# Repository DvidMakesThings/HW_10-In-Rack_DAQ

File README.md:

# DataForge-Pi - The Raspberry integrated DAQ Project

## Introduction

In the current market, finding a DAQ specifically designed for 10-inch racks is quite challenging. Most available options are tailored for 19-inch racks, which are significantly larger and not suitable for more compact setups. Recognizing this gap, I embarked on a project to create a DAQ solution that fits perfectly in a 10-inch rack while still providing all the necessary features and functionalities. The goal of this project is not only to address the size constraints but also to keep the costs low and make the design accessible to everyone. 

## Development Phases

| Phase                                | Status   |
| ------------------------------------ | -------- |
| **PCB Design & Prototyping**         |  |
| **Design Review**                    |  |
| **Enclosure Design**                 |  |
| **Order PCB**                        |  |
| **Prototyping and Hardware Testing** |  |
| **Initial Firmware Development**     |  |
| **Enclosure Testing & Ventilation**  |  |
| **Web-Based UI for Control**         |  |
| **Power Logging & Alerts**           |  |
| **Production Optimization**          |  |

## Features

Key features of the CM5 are as follows (for more details, refer to the [CM5 datasheet](docs/Datasheets/Raspberry-CM5_Datasheet.pdf)):

- Broadcom BCM2712, quad core Cortex-A76 (ARMv8) 64-bit SoC @ 2.4GHz
- Small Footprint 55mm × 40mm × 4.7mm module
  - 4 × M2.5 mounting holes
- 4kp60 HEVC decoder
- OpenGL ES 3.1 graphics, Vulkan 1.2
- Options for 2GB, 4GB, or 8GB LPDDR4-4267 SDRAM with ECC (see Appendix D)
- Options for 0GB (CM5Lite), 16GB, or 32GB eMMC flash memory (see Appendix D)
  - Peak eMMC bandwidth 400MBps (four times faster than previous Compute Modules)
- Option (see Appendix D) for certified radio module with:
  - 2.4 GHz, 5.0 GHz IEEE 802.11 b/g/n/ac wireless
  - Bluetooth 5.0, BLE
  - On board electronic switch to select between PCB trace or external antenna
- Gigabit Ethernet PHY supporting IEEE 1588
- 1 × PCIe 1-lane Host, Gen 2 (5Gbps)
- 1 × USB 2.0 port (high speed)
- 2 × USB 3.0 ports, supporting simultaneous 5Gbps operation
- Up to 30 × GPIO supporting either 1.8V or 3.3V signalling and peripheral options:
  - Up to 5 × UART
  - Up to 5 × I2C
  - Up to 5 × SPI
  - 1 × SDIO interface
  - 1 × DPI (parallel RGB display)
  - 1 × I2S
  - Up to 4 × PWM channels
  - Up to 3 × GPCLK outputs
- 2 × HDMI 2.0 ports (supports up to 4Kp60 on each port simultaneously)
- 2 × 4-lane MIPI ports
  - Supporting both DSI (display port) and CSI-2 (camera port)
- 1 × SDIO 2.0 (CM5Lite)
- Single +5V PSU input supports USB PD for up to 5A @ 5V
- Real-time clock (RTC), powered from external battery

## DAQ Specifications

### Analog Input (16 Channels)

The analog input section of the DAQ system is designed to provide high precision and flexibility for various applications. It features 16 channels of analog input, each capable of high-resolution data acquisition.

**Key Components:**
- **External 14-bit ADC:** The ADS9234RIRHBR is a 14-bit, 3.5-MSPS dual SAR ADC with simultaneous sampling, internal reference, and enhanced SPI, ensuring accurate and reliable measurements.
- **Multiplexers:** 2 × DG409 are employed for flexible channel selection, allowing the system to switch between different input channels efficiently.
- **Programmable Gain Amplifiers (PGA):** ADA4254ACPZ are used to provide scalable input ranges, enabling the system to handle a wide variety of signal amplitudes.

### Analog Output (8 Channels)

The analog output section is designed to provide precise and stable output signals. It features 8 channels of analog output, each capable of high-resolution signal generation.

**Key Components:**
- **External 16-bit DAC:** The DAC8568 is used for precision outputs, ensuring accurate and stable signal generation.
- **Operational Amplifiers:** TLV2372 are used for buffering and output stability, providing reliable and consistent performance.

### Digital IO (32 Channels)

The digital IO section is designed to provide versatile and robust digital input and output capabilities. It features 32 channels of digital IO, each capable of handling various voltage levels and signal types.

**Key Components:**
- **Bidirectional Voltage-Level Translators:** LSF0108-Q1 are used for multi-voltage compatibility, allowing the system to interface with different voltage levels.
- **Direct GPIO Support:** The RP2040 provides simple and robust design for direct GPIO support, ensuring reliable digital IO performance.

### Constants

- **ADC Sampling Rate:** 3.5 MSPS (Maximum sampling rate of ADS9234R)
- **ADC Nyquist Limit:** 1.75 MHz (Nyquist bandwidth for ADC)
- **PGA Bandwidth:** 10 MHz (Maximum bandwidth of ADA4254 at Gain = 1)
- **DG409 Transition Time:** 160 ns (Transition time for DG409)
- **ADA4254 Transition Time:** 200 ns (Transition time for ADA4254)

### Bandwidth for Each Gain Setting

The bandwidth for each gain setting is determined by the combination of the ADC's Nyquist limit and the PGA's frequency response. For gains less than or equal to 1, the bandwidth is capped by the ADC's Nyquist limit. For gains greater than 1, the bandwidth is limited by the PGA's frequency response.

- **Gain = 1/16:** Bandwidth = 1.75 MHz (Capped by ADC)
- **Gain = 1/8:** Bandwidth = 1.75 MHz (Capped by ADC)
- **Gain = 1/4:** Bandwidth = 1.75 MHz (Capped by ADC)
- **Gain = 1/2:** Bandwidth = 1.75 MHz (Capped by ADC)
- **Gain = 1:** Bandwidth = 1.75 MHz (Capped by ADC)
- **Gain = 2:** Bandwidth = 1.75 MHz (Capped by ADC)
- **Gain = 4:** Bandwidth = 1.75 MHz (Capped by ADC)
- **Gain = 8:** Bandwidth = 1.25 MHz (PGA Limited)
- **Gain = 16:** Bandwidth = 625 kHz (PGA Limited)
- **Gain = 32:** Bandwidth = 312.5 kHz (PGA Limited)
- **Gain = 64:** Bandwidth = 156.25 kHz (PGA Limited)
- **Gain = 128:** Bandwidth = 78.125 kHz (PGA Limited)

### Notes

- For Gains ≤ 1, bandwidth is capped by ADC's Nyquist limit (1.75 MHz).
- For Gains > 1, bandwidth is limited by the PGA's frequency response.
- Transition delays (DG409 + ADA4254) are factored into the calculation.

### Input Ranges for Different Gains

The input ranges for different gain settings are determined by the reference voltage (VREF), positive supply voltage (V+), and negative supply voltage (V-). For this system, VREF is set to 2.5V, V+ is set to +12V, and V- is set to -12V.

| Gain | Differential Input Range (±V) | Positive Input Range (0 to V) | Negative Input Range (0 to -V) | Max Bandwidth (Hz) |
|------|-------------------------------|-------------------------------|-------------------------------|--------------------|
| 1/16 | ±80.0                         | 0 to 40.0                     | 0 to -40.0                    | 1,750,000          |
| 1/8  | ±40.0                         | 0 to 20.0                     | 0 to -20.0                    | 1,750,000          |
| 1/4  | ±20.0                         | 0 to 10.0                     | 0 to -10.0                    | 1,750,000          |
| 1/2  | ±10.0                         | 0 to 5.0                      | 0 to -5.0                     | 1,750,000          |
| 1    | ±5.0                          | 0 to 2.5                      | 0 to -2.5                     | 1,750,000          |
| 2    | ±2.5                          | 0 to 1.25                     | 0 to -1.25                    | 1,750,000          |
| 4    | ±1.25                         | 0 to 0.625                    | 0 to -0.625                   | 1,750,000          |
| 8    | ±0.625                        | 0 to 0.3125                   | 0 to -0.3125                  | 1,250,000          |
| 16   | ±0.3125                       | 0 to 0.15625                  | 0 to -0.15625                 | 625,000            |
| 32   | ±0.15625                      | 0 to 0.078125                 | 0 to -0.078125                | 312,500            |
| 64   | ±0.078125                     | 0 to 0.0390625                | 0 to -0.0390625               | 156,250            |
| 128  | ±0.0390625                    | 0 to 0.01953125               | 0 to -0.01953125              | 78,125             |

## Getting Started

Refer to the datasheets and manuals in the `docs` folder for detailed information on the components and usage instructions.

## License

This project is licensed under the GPL3 License. See the LICENSE file for details.

## Contact

For questions or feedback:

- Email: s.dvid@hotmail.com
- GitHub: [DvidMakesThings](https://github.com/DvidMakesThings)

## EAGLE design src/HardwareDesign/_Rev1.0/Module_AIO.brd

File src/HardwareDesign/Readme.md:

# # %PROJECT_NAME% Project Hardware Design Files
## Contents
This folder contains the hardware design files for the %PROJECT_NAME% project. The main components include:
- Schematic diagrams
- PCB layouts
- Bill of Materials (BOM)
- Gerber files
## Usage
To use these hardware design files:
1. Open the schematic diagrams and PCB layouts using EAGLE software.
2. Review the Bill of Materials for required components.
3. Follow the design files to assemble and test the hardware.
4. Use the Gerber files for PCB manufacturing.
## License
This project is licensed under the MIT License.
## Contact
For any questions or feedback, please contact:
- Email: [s.dvid@hotmail.com](mailto:s.dvid@hotmail.com)
- GitHub: [DvidMakesThings](https://github.com/DvidMakesThings)

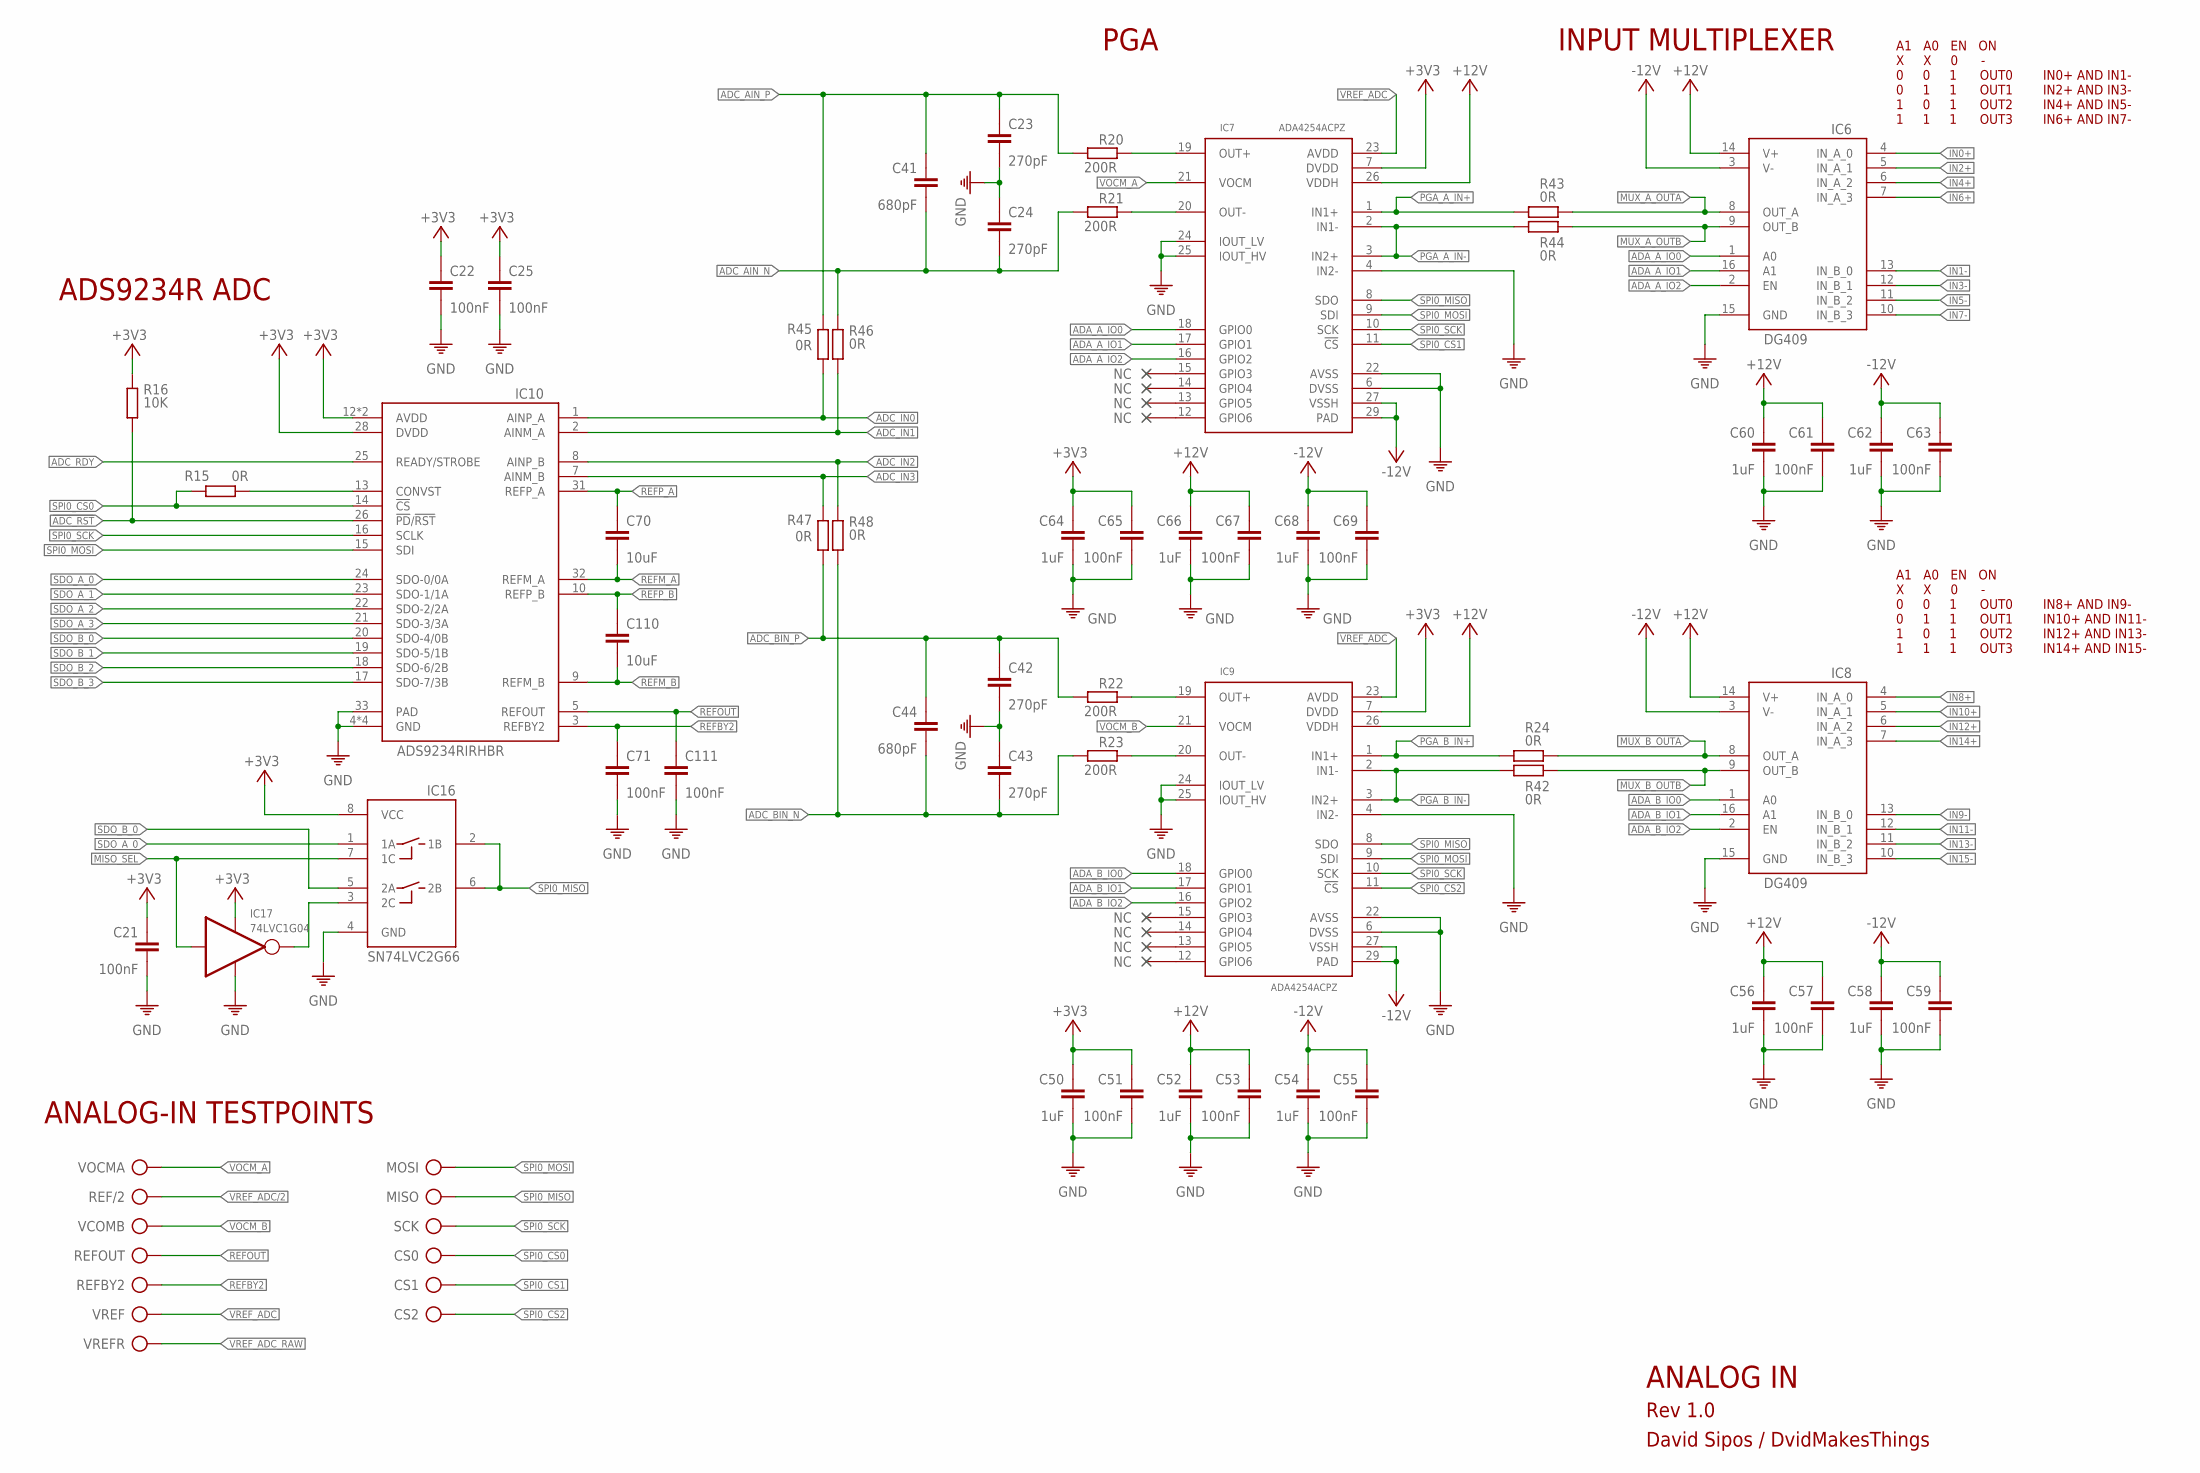
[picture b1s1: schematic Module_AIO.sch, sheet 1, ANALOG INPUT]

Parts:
C21, C22, C25, C51, C53, C55, C57, C59, C61, C63, C65, C67, C69, C71, C111: 100nF; C0402
C23, C24, C42, C43: 270pF; C0402
C41, C44: 680pF; C0402
C50, C52, C54, C56, C58, C60, C62, C64, C66, C68: 1uF; C0402
C70, C110: 10uF; C0402
CS0, CS1, CS2: TP
IC6, IC8: DG409; TSSOP2
IC7, IC9: ADA4254ACPZ; QFN50P500X500X75-29T314N
IC10: ADS9234RIRHBR; VQFN32-5X5
IC16: SN74LVC2G66; SOP50P310X90-8N
IC17: 74LVC1G04; SOT95P280X145-5N
MISO: TP
MOSI: TP
R15, R24, R42, R43, R44, R45, R46, R47, R48: 0R; 0402
R16: 10K; 0402
R20, R21, R22, R23: 200R; 0402
REF/2: TP
REFBY2: TP
REFOUT: TP
SCK: TP
VCOMB: TP
VOCMA: TP
VREF: TP
VREFR: TP

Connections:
!ADC_RST: IC10.26 (!PD!/!RST), R16.2; also elsewhere on the board
!MISO_SEL: IC16.3 (2C), IC17.4 (OUT)
+3V3: C21.1, C22.1, C25.1, C50.1, C51.1, C64.1, C65.1, IC7.7 (DVDD), IC9.7 (DVDD), IC10.12 (AVDD), IC10.28 (DVDD), IC10.29 (AVDD), IC16.8 (VCC), IC17.5 (V+), R16.1; also elsewhere on the board
+12V: C52.1, C53.1, C56.1, C57.1, C60.1, C61.1, C66.1, C67.1, IC6.14 (V+), IC7.26 (VDDH), IC8.14 (V+), IC9.26 (VDDH); also elsewhere on the board
-12V: C54.1, C55.1, C58.1, C59.1, C62.1, C63.1, C68.1, C69.1, IC6.3 (V-), IC7.27 (VSSH), IC7.29 (PAD), IC8.3 (V-), IC9.27 (VSSH), IC9.29 (PAD); also elsewhere on the board
ADA_A_IO0: IC6.1 (A0), IC7.18 (GPIO0)
ADA_A_IO1: IC6.16 (A1), IC7.17 (GPIO1)
ADA_A_IO2: IC6.2 (EN), IC7.16 (GPIO2)
ADA_B_IO0: IC8.1 (A0), IC9.18 (GPIO0)
ADA_B_IO1: IC8.16 (A1), IC9.17 (GPIO1)
ADA_B_IO2: IC8.2 (EN), IC9.16 (GPIO2)
ADC_AIN_N: C24.2, C41.2, R21.1, R46.1
ADC_AIN_P: C23.1, C41.1, R20.1, R45.2
ADC_BIN_N: C43.2, C44.2, R23.1, R48.2
ADC_BIN_P: C42.1, C44.1, R22.1, R47.1
ADC_IN0: IC10.1 (AINP_A), R45.1
ADC_IN1: IC10.2 (AINM_A), R46.2
ADC_IN2: IC10.8 (AINP_B), R48.1
ADC_IN3: IC10.7 (AINM_B), R47.2
ADC_RDY: IC10.25 (READY/STROBE); also elsewhere on the board
GND: C21.2, C22.2, C23.2, C24.1, C25.2, C42.2, C43.1, C50.2, C51.2, C52.2, C53.2, C54.2, C55.2, C56.2, C57.2, C58.2, C59.2, C60.2, C61.2, C62.2, C63.2, C64.2, C65.2, C66.2, C67.2, C68.2, C69.2, C71.2, C111.2, IC6.15 (GND), IC7.4 (IN2-), IC7.6 (DVSS), IC7.22 (AVSS), IC7.24 (IOUT_LV), IC7.25 (IOUT_HV), IC8.15 (GND), IC9.4 (IN2-), IC9.6 (DVSS), IC9.22 (AVSS), IC9.24 (IOUT_LV), IC9.25 (IOUT_HV), IC10.4 (GND), IC10.11 (GND), IC10.27 (GND), IC10.30 (GND), IC10.33 (PAD), IC16.4 (GND), IC17.3 (V-); also elsewhere on the board
IN0+: IC6.4 (IN_A_0); also elsewhere on the board
IN1-: IC6.13 (IN_B_0); also elsewhere on the board
IN2+: IC6.5 (IN_A_1); also elsewhere on the board
IN3-: IC6.12 (IN_B_1); also elsewhere on the board
IN4+: IC6.6 (IN_A_2); also elsewhere on the board
IN5-: IC6.11 (IN_B_2); also elsewhere on the board
IN6+: IC6.7 (IN_A_3); also elsewhere on the board
IN7-: IC6.10 (IN_B_3); also elsewhere on the board
IN8+: IC8.4 (IN_A_0); also elsewhere on the board
IN9-: IC8.13 (IN_B_0); also elsewhere on the board
IN10+: IC8.5 (IN_A_1); also elsewhere on the board
IN11-: IC8.12 (IN_B_1); also elsewhere on the board
IN12+: IC8.6 (IN_A_2); also elsewhere on the board
IN13-: IC8.11 (IN_B_2); also elsewhere on the board
IN14+: IC8.7 (IN_A_3); also elsewhere on the board
IN15-: IC8.10 (IN_B_3); also elsewhere on the board
MISO_SEL: IC16.7 (1C), IC17.2 (IN); also elsewhere on the board
MUX_A_OUTA: IC6.8 (OUT_A), R43.2
MUX_A_OUTB: IC6.9 (OUT_B), R44.1
MUX_B_OUTA: IC8.8 (OUT_A), R24.2
MUX_B_OUTB: IC8.9 (OUT_B), R42.1
unnamed: IC7.19 (OUT+), R20.2
unnamed: IC7.20 (OUT-), R21.2
unnamed: IC9.19 (OUT+), R22.2
unnamed: IC9.20 (OUT-), R23.2
unnamed: IC10.13 (CONVST), R15.2
PGA_A_IN+: IC7.1 (IN1+), R43.1
PGA_A_IN-: IC7.2 (IN1-), IC7.3 (IN2+), R44.2
PGA_B_IN+: IC9.1 (IN1+), R24.1
PGA_B_IN-: IC9.2 (IN1-), IC9.3 (IN2+), R42.2
REFBY2: C71.1, IC10.3 (REFBY2), REFBY2.TP
REFM_A: C70.2, IC10.32 (REFM_A)
REFM_B: C110.2, IC10.9 (REFM_B)
REFOUT: C111.1, IC10.5 (REFOUT), REFOUT.TP
REFP_A: C70.1, IC10.31 (REFP_A)
REFP_B: C110.1, IC10.10 (REFP_B)
SDO_A_0: IC10.24 (SDO-0/0A), IC16.1 (1A); also elsewhere on the board
SDO_A_1: IC10.23 (SDO-1/1A); also elsewhere on the board
SDO_A_2: IC10.22 (SDO-2/2A); also elsewhere on the board
SDO_A_3: IC10.21 (SDO-3/3A); also elsewhere on the board
SDO_B_0: IC10.20 (SDO-4/0B), IC16.5 (2A); also elsewhere on the board
SDO_B_1: IC10.19 (SDO-5/1B); also elsewhere on the board
SDO_B_2: IC10.18 (SDO-6/2B); also elsewhere on the board
SDO_B_3: IC10.17 (SDO-7/3B); also elsewhere on the board
SPI0_CS0: CS0.TP, IC10.14 (!CS), R15.1; also elsewhere on the board
SPI0_CS1: CS1.TP, IC7.11 (!CS); also elsewhere on the board
SPI0_CS2: CS2.TP, IC9.11 (!CS); also elsewhere on the board
SPI0_MISO: IC7.8 (SDO), IC9.8 (SDO), IC16.2 (1B), IC16.6 (2B), MISO.TP; also elsewhere on the board
SPI0_MOSI: IC7.9 (SDI), IC9.9 (SDI), IC10.15 (SDI), MOSI.TP; also elsewhere on the board
SPI0_SCK: IC7.10 (SCK), IC9.10 (SCK), IC10.16 (SCLK), SCK.TP; also elsewhere on the board
VOCM_A: IC7.21 (VOCM), VOCMA.TP; also elsewhere on the board
VOCM_B: IC9.21 (VOCM), VCOMB.TP; also elsewhere on the board
VREF_ADC: IC7.23 (AVDD), IC9.23 (AVDD), VREF.TP; also elsewhere on the board
VREF_ADC/2: REF/2.TP; also elsewhere on the board
VREF_ADC_RAW: VREFR.TP; also elsewhere on the board

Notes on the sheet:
ADS9234R ADC
A1 A0 EN ON
X X 0 -
0 0 1 OUT0
0 1 1 OUT1
1 0 1 OUT2
1 1 1 OUT3
IN0+ AND IN1-
IN2+ AND IN3-
IN4+ AND IN5-
IN6+ AND IN7-
IN8+ AND IN9-
IN10+ AND IN11-
IN12+ AND IN13-
IN14+ AND IN15-
ANALOG-IN TESTPOINTS
PGA
INPUT MULTIPLEXER
ANALOG IN
Rev 1.0
David Sipos / DvidMakesThings

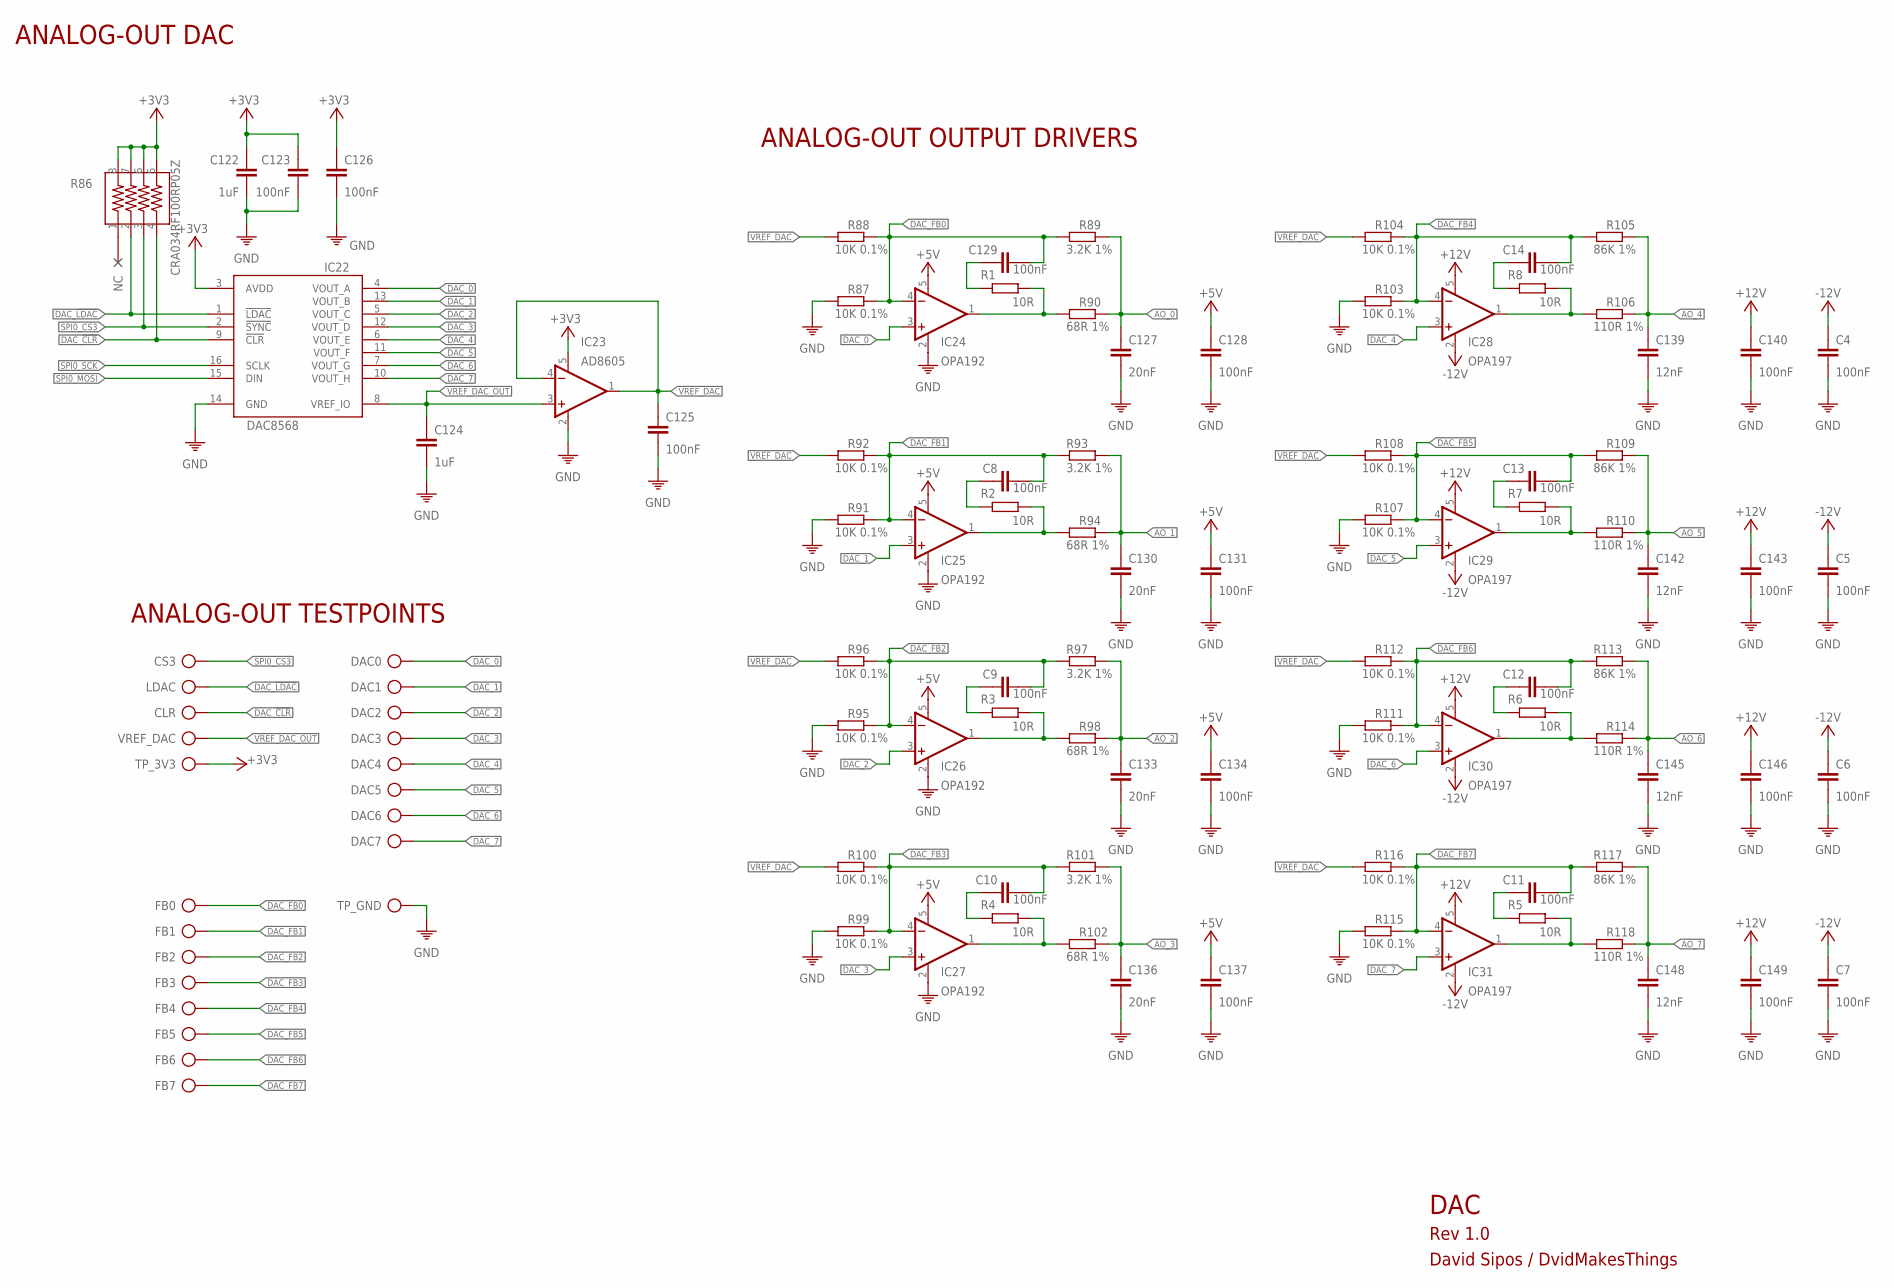
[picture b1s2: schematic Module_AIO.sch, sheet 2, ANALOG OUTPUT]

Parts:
C4, C5, C6, C7, C8, C9, C10, C11, C12, C13, C14, C123, C125, C126, C128, C129, C131, C134, C137, C140, C143, C146, C149: 100nF; C0402
C122, C124: 1uF; C0402
C127, C130, C133, C136: 20nF; C0402
C139, C142, C145, C148: 12nF; C0402
CLR: TP
CS3: TP
DAC0, DAC1, DAC2, DAC3, DAC4, DAC5, DAC6, DAC7: TP
FB0, FB1, FB2, FB3, FB4, FB5, FB6, FB7: TP
IC22: DAC8568; TSSOP16
IC23: AD8605; SOT23-5
IC24, IC25, IC26, IC27: OPA192; SOT23-5
IC28, IC29, IC30, IC31: OPA197; SOT23-5
LDAC: TP
R1, R2, R3, R4, R5, R6, R7, R8: 10R; 0402
R86: CRA034RF100RP05Z; YC164-JR-0733RL
R87, R88, R91, R92, R95, R96, R99, R100, R103, R104, R107, R108, R111, R112, R115, R116: 10K 0.1%; 0402
R89, R93, R97, R101: 3.2K 1%; 0402
R90, R94, R98, R102: 68R 1%; 0402
R105, R109, R113, R117: 86K 1%; 0402
R106, R110, R114, R118: 110R 1%; 0402
TP_3V3: TP
TP_GND: TP
VREF_DAC: TP

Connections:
+3V3: C122.1, C123.1, C126.1, IC22.3 (AVDD), IC23.5 (V+), R86.5, R86.6, R86.7, R86.8, TP_3V3.TP; also elsewhere on the board
+5V: C128.1, C131.1, C134.1, C137.1, IC24.5 (V+), IC25.5 (V+), IC26.5 (V+), IC27.5 (V+); also elsewhere on the board
+12V: C140.1, C143.1, C146.1, C149.1, IC28.5 (V+), IC29.5 (V+), IC30.5 (V+), IC31.5 (V+); also elsewhere on the board
-12V: C4.1, C5.1, C6.1, C7.1, IC28.2 (V-), IC29.2 (V-), IC30.2 (V-), IC31.2 (V-); also elsewhere on the board
AO_0: C127.1, R89.2, R90.2; also elsewhere on the board
AO_1: C130.1, R93.2, R94.2; also elsewhere on the board
AO_2: C133.1, R97.2, R98.2; also elsewhere on the board
AO_3: C136.1, R101.2, R102.2; also elsewhere on the board
AO_4: C139.1, R105.2, R106.2; also elsewhere on the board
AO_5: C142.1, R109.2, R110.2; also elsewhere on the board
AO_6: C145.1, R113.2, R114.2; also elsewhere on the board
AO_7: C148.1, R117.2, R118.2; also elsewhere on the board
DAC_0: DAC0.TP, IC22.4 (VOUT_A), IC24.3 (+IN)
DAC_1: DAC1.TP, IC22.13 (VOUT_B), IC25.3 (+IN)
DAC_2: DAC2.TP, IC22.5 (VOUT_C), IC26.3 (+IN)
DAC_3: DAC3.TP, IC22.12 (VOUT_D), IC27.3 (+IN)
DAC_4: DAC4.TP, IC22.6 (VOUT_E), IC28.3 (+IN)
DAC_5: DAC5.TP, IC22.11 (VOUT_F), IC29.3 (+IN)
DAC_6: DAC6.TP, IC22.7 (VOUT_G), IC30.3 (+IN)
DAC_7: DAC7.TP, IC22.10 (VOUT_H), IC31.3 (+IN)
DAC_!CLR: CLR.TP, IC22.9 (!CLR), R86.4; also elsewhere on the board
DAC_!LDAC: IC22.1 (!LDAC), LDAC.TP, R86.2; also elsewhere on the board
DAC_FB0: C129.2, FB0.TP, IC24.4 (-IN), R87.2, R88.2, R89.1
DAC_FB1: C8.2, FB1.TP, IC25.4 (-IN), R91.2, R92.2, R93.1
DAC_FB2: C9.2, FB2.TP, IC26.4 (-IN), R95.2, R96.2, R97.1
DAC_FB3: C10.2, FB3.TP, IC27.4 (-IN), R99.2, R100.2, R101.1
DAC_FB4: C14.2, FB4.TP, IC28.4 (-IN), R103.2, R104.2, R105.1
DAC_FB5: C13.2, FB5.TP, IC29.4 (-IN), R107.2, R108.2, R109.1
DAC_FB6: C12.2, FB6.TP, IC30.4 (-IN), R111.2, R112.2, R113.1
DAC_FB7: C11.2, FB7.TP, IC31.4 (-IN), R115.2, R116.2, R117.1
GND: C4.2, C5.2, C6.2, C7.2, C122.2, C123.2, C124.2, C125.2, C126.2, C127.2, C128.2, C130.2, C131.2, C133.2, C134.2, C136.2, C137.2, C139.2, C140.2, C142.2, C143.2, C145.2, C146.2, C148.2, C149.2, IC22.14 (GND), IC23.2 (V-), IC24.2 (V-), IC25.2 (V-), IC26.2 (V-), IC27.2 (V-), R87.1, R91.1, R95.1, R99.1, R103.1, R107.1, R111.1, R115.1, TP_GND.TP; also elsewhere on the board
unnamed: C129.1, R1.2
unnamed: C8.1, R2.2
unnamed: C9.1, R3.2
unnamed: C10.1, R4.2
unnamed: IC24.1 (OUT), R1.1, R90.1
unnamed: C11.1, R5.2
unnamed: IC25.1 (OUT), R2.1, R94.1
unnamed: C12.1, R6.2
unnamed: IC26.1 (OUT), R3.1, R98.1
unnamed: IC27.1 (OUT), R4.1, R102.1
unnamed: C13.1, R7.2
unnamed: IC28.1 (OUT), R8.1, R106.1
unnamed: IC29.1 (OUT), R7.1, R110.1
unnamed: C14.1, R8.2
unnamed: IC30.1 (OUT), R6.1, R114.1
unnamed: IC31.1 (OUT), R5.1, R118.1
SPI0_CS3: CS3.TP, IC22.2 (!SYNC), R86.3; also elsewhere on the board
SPI0_MOSI: IC22.15 (DIN); also elsewhere on the board
SPI0_SCK: IC22.16 (SCLK); also elsewhere on the board
VREF_DAC: C125.1, IC23.1 (OUT), IC23.4 (-IN), R88.1, R92.1, R96.1, R100.1, R104.1, R108.1, R112.1, R116.1
VREF_DAC_OUT: C124.1, IC22.8 (VREF_IO), IC23.3 (+IN), VREF_DAC.TP

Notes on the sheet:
ANALOG-OUT TESTPOINTS
ANALOG-OUT DAC
ANALOG-OUT OUTPUT DRIVERS
DAC
Rev 1.0
David Sipos / DvidMakesThings

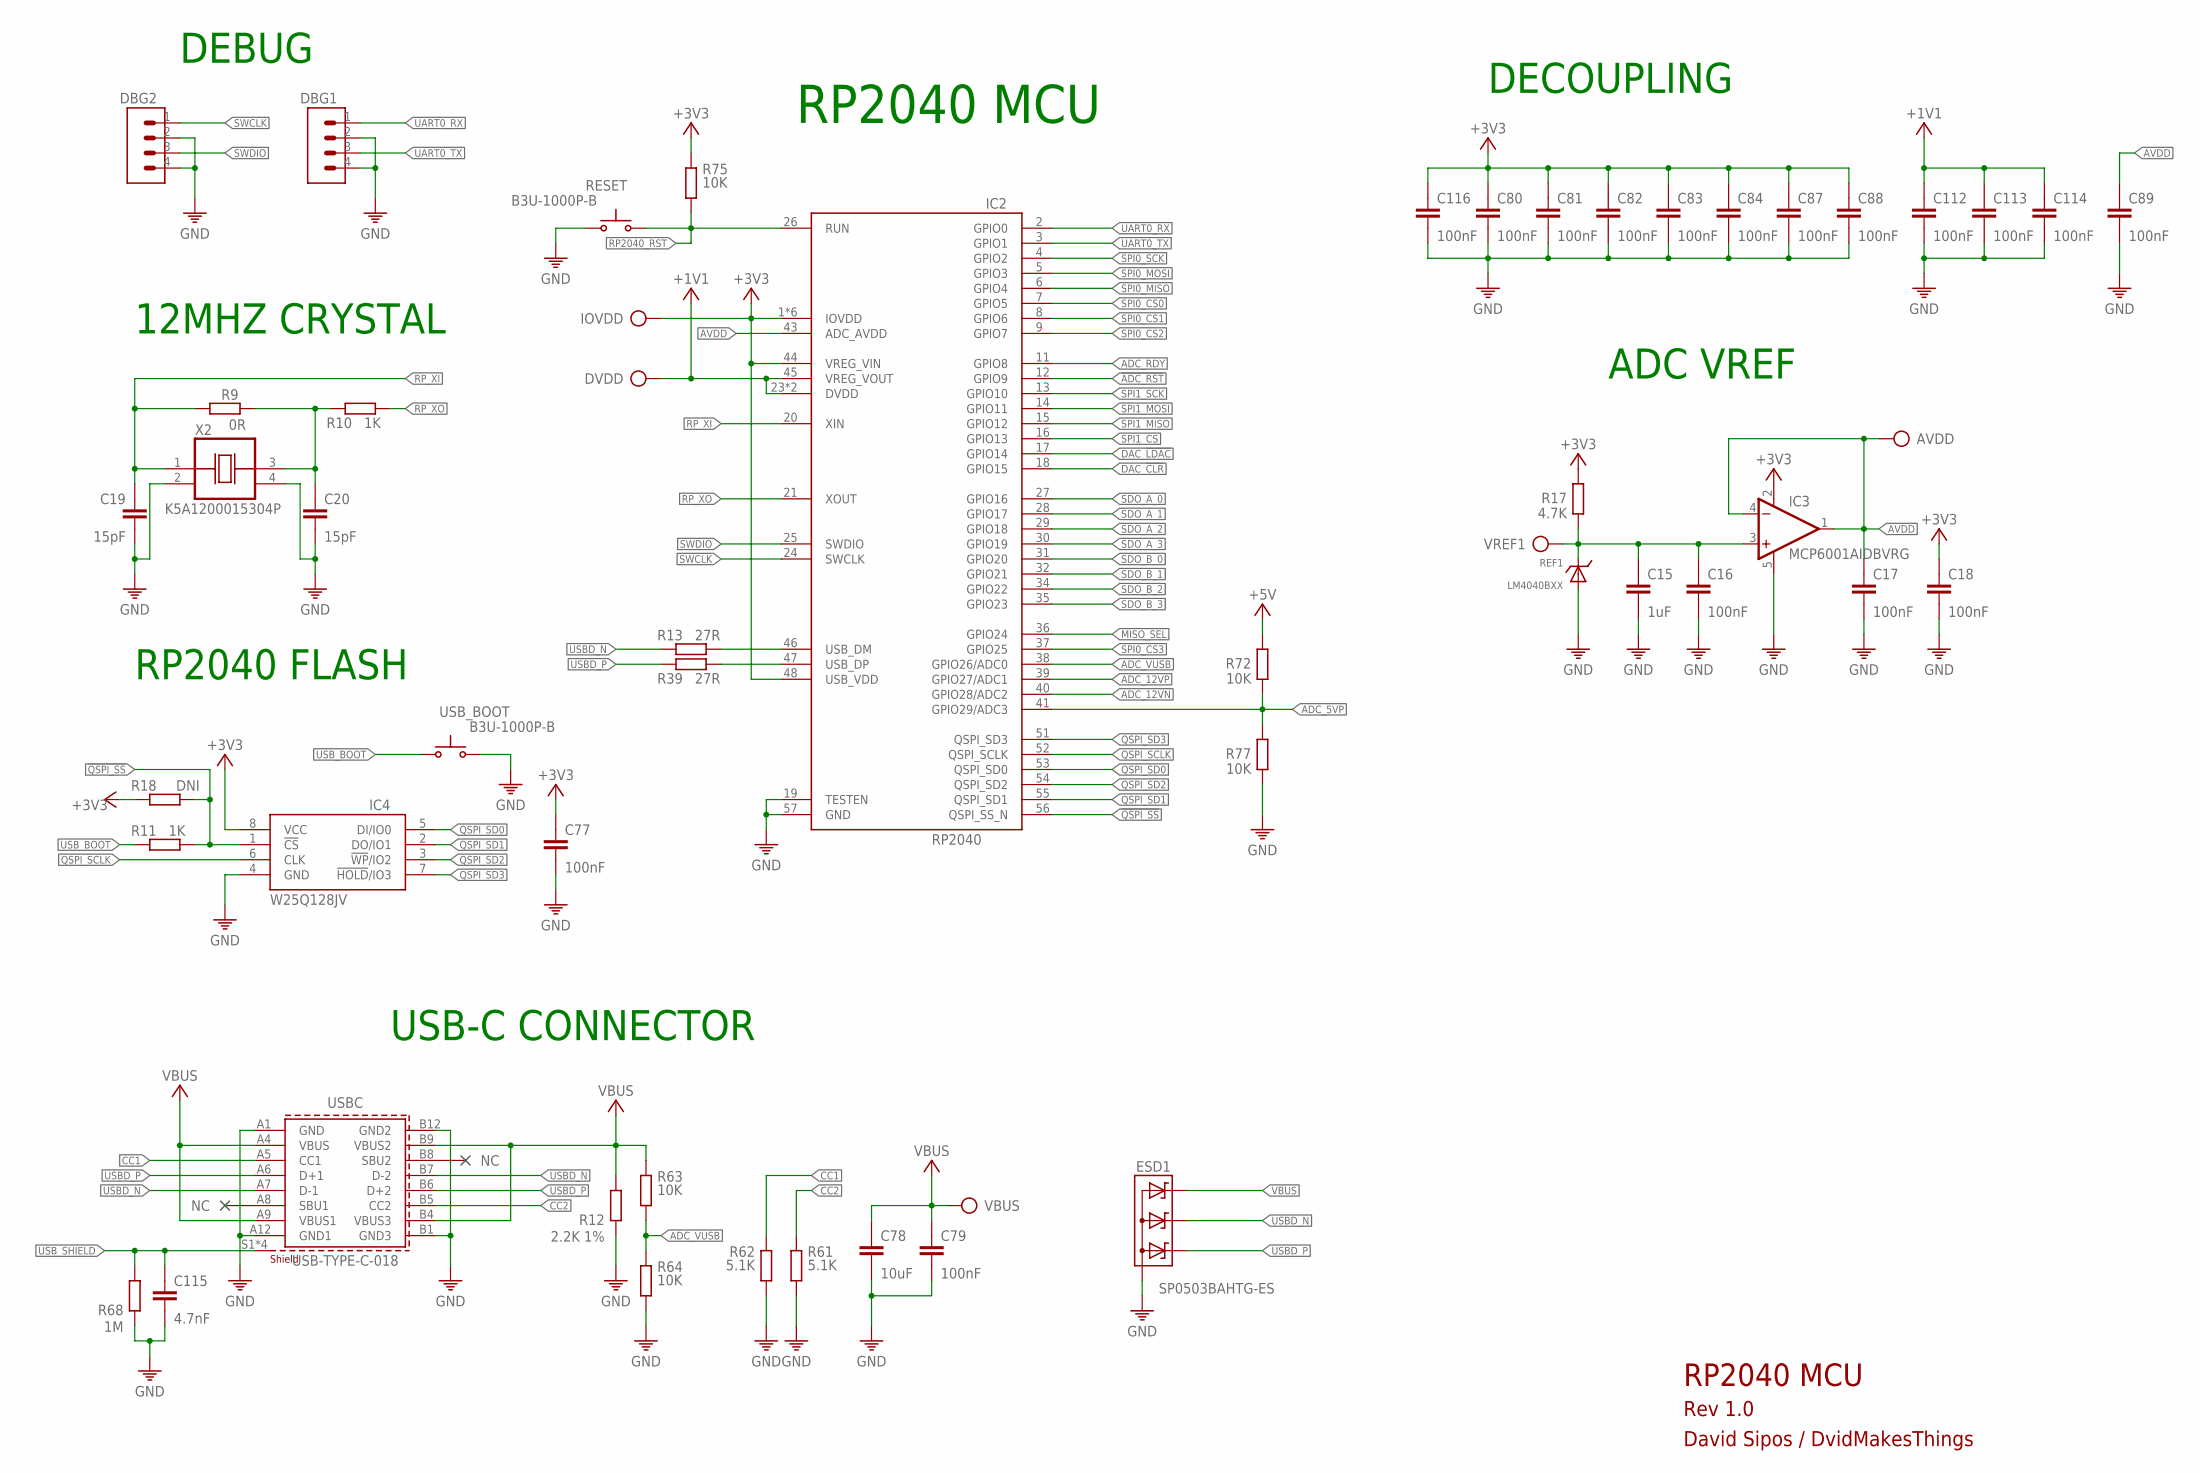
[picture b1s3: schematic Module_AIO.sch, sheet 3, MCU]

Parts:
AVDD: TP
C15: 1uF; C0402
C16, C17, C18, C77, C80, C81, C82, C83, C84, C87, C88, C89, C112, C113, C114, C116: 100nF; C0402
C19, C20: 15pF; C0402
C78: 10uF; 0805
C79: 100nF; 0402
C115: 4.7nF; 0402
DBG1, DBG2: CON-1X4; 1X4
DVDD: TP
ESD1: SP0503BAHTG-ES; SOT143
IC2: RP2040; QFN40P700X700X100-57T510
IC3: MCP6001AIDBVRG; SOT23-5
IC4: W25Q128JVPIQ; SON127P600X500X75-8N
IOVDD: TP
R9: 0R; 0402
R10, R11: 1K; 0402
R12: 2.2K 1%; 0402
R13, R39: 27R; 0402
R17: 4.7K; 0402
R18: DNI; 0402
R61, R62: 5.1K; 0402
R63, R64, R72, R75, R77: 10K; 0402
R68: 1M; 0402
REF1: LM4040BXX; SOT23
RESET: B3U-1000P-B; SWITCH-OMRON_B3U-1000P
USBC: USB-TYPE-C-018; 629722000214
USB_BOOT: B3U-1000P-B; SWITCH-OMRON_B3U-1000P
VBUS: TP
VREF1: TP
X2: K5A1200015304P; OSCCC500X320X130

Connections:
!ADC_RST: IC2.12 (GPIO9); also elsewhere on the board
!QSPI_SS: IC2.56 (QSPI_SS_N), IC4.1 (!CS), R11.2, R18.1
+1V1: C112.1, C113.1, C114.1, DVDD.TP, IC2.23 (DVDD), IC2.45 (VREG_VOUT), IC2.50 (DVDD)
+3V3: C18.1, C77.1, C80.1, C81.1, C82.1, C83.1, C84.1, C87.1, C88.1, C116.1, IC2.1 (IOVDD), IC2.10 (IOVDD), IC2.22 (IOVDD), IC2.33 (IOVDD), IC2.42 (IOVDD), IC2.44 (VREG_VIN), IC2.48 (USB_VDD), IC2.49 (IOVDD), IC3.2 (V+), IC4.8 (VCC), IOVDD.TP, R17.2, R18.2, R75.1; also elsewhere on the board
+5V: R72.2; also elsewhere on the board
ADC_5VP: IC2.41 (GPIO29/ADC3), R72.1, R77.2
ADC_12VN: IC2.40 (GPIO28/ADC2); also elsewhere on the board
ADC_12VP: IC2.39 (GPIO27/ADC1); also elsewhere on the board
ADC_RDY: IC2.11 (GPIO8); also elsewhere on the board
ADC_VUSB: IC2.38 (GPIO26/ADC0), R63.2, R64.1
AVDD: AVDD.TP, C17.1, C89.1, IC2.43 (ADC_AVDD), IC3.1 (OUT), IC3.4 (-IN)
CC1: R62.1, USBC.A5 (CC1)
CC2: R61.1, USBC.B5 (CC2)
DAC_!CLR: IC2.18 (GPIO15); also elsewhere on the board
DAC_!LDAC: IC2.17 (GPIO14); also elsewhere on the board
GND: C15.2, C16.2, C17.2, C18.2, C19.2, C20.2, C77.2, C78.2, C79.2, C80.2, C81.2, C82.2, C83.2, C84.2, C87.2, C88.2, C89.2, C112.2, C113.2, C114.2, C115.2, C116.2, DBG1.2, DBG1.4, DBG2.2, DBG2.4, ESD1.1 (A), IC2.19 (TESTEN), IC2.57 (GND), IC3.5 (V-), IC4.4 (GND), R12.2, R61.2, R62.2, R64.2, R68.2, R77.1, REF1.2 (A), REF1.3 (A), RESET.2 (S), USBC.A1 (GND), USBC.A12 (GND1), USBC.B1 (GND3), USBC.B12 (GND2), USB_BOOT.2 (S), X2.2 (VSS), X2.4 (VDD); also elsewhere on the board
MISO_SEL: IC2.36 (GPIO24); also elsewhere on the board
unnamed: C20.1, R9.2, R10.1, X2.3 (OUT)
QSPI_SCLK: IC2.52 (QSPI_SCLK), IC4.6 (CLK)
QSPI_SD0: IC2.53 (QSPI_SD0), IC4.5 (DI/IO0)
QSPI_SD1: IC2.55 (QSPI_SD1), IC4.2 (DO/IO1)
QSPI_SD2: IC2.54 (QSPI_SD2), IC4.3 (!WP!/IO2)
QSPI_SD3: IC2.51 (QSPI_SD3), IC4.7 (!HOLD!/IO3)
RP2040_RST: IC2.26 (RUN), R75.2, RESET.1; also elsewhere on the board
RP_USBD_N: IC2.46 (USB_DM), R13.2
RP_USBD_P: IC2.47 (USB_DP), R39.2
RP_XI: C19.1, IC2.20 (XIN), R9.1, X2.1 (CON)
RP_XO: IC2.21 (XOUT), R10.2
SDO_A_0: IC2.27 (GPIO16); also elsewhere on the board
SDO_A_1: IC2.28 (GPIO17); also elsewhere on the board
SDO_A_2: IC2.29 (GPIO18); also elsewhere on the board
SDO_A_3: IC2.30 (GPIO19); also elsewhere on the board
SDO_B_0: IC2.31 (GPIO20); also elsewhere on the board
SDO_B_1: IC2.32 (GPIO21); also elsewhere on the board
SDO_B_2: IC2.34 (GPIO22); also elsewhere on the board
SDO_B_3: IC2.35 (GPIO23); also elsewhere on the board
SPI0_CS0: IC2.7 (GPIO5); also elsewhere on the board
SPI0_CS1: IC2.8 (GPIO6); also elsewhere on the board
SPI0_CS2: IC2.9 (GPIO7); also elsewhere on the board
SPI0_CS3: IC2.37 (GPIO25); also elsewhere on the board
SPI0_MISO: IC2.6 (GPIO4); also elsewhere on the board
SPI0_MOSI: IC2.5 (GPIO3); also elsewhere on the board
SPI0_SCK: IC2.4 (GPIO2); also elsewhere on the board
SPI1_CS: IC2.16 (GPIO13); also elsewhere on the board
SPI1_MISO: IC2.15 (GPIO12); also elsewhere on the board
SPI1_MOSI: IC2.14 (GPIO11); also elsewhere on the board
SPI1_SCK: IC2.13 (GPIO10); also elsewhere on the board
SWCLK: DBG2.1, IC2.24 (SWCLK); also elsewhere on the board
SWDIO: DBG2.3, IC2.25 (SWDIO); also elsewhere on the board
UART0_RX: DBG1.1, IC2.2 (GPIO0); also elsewhere on the board
UART0_TX: DBG1.3, IC2.3 (GPIO1); also elsewhere on the board
USBD_N: ESD1.3 (C2), R13.1, USBC.A7 (D-1), USBC.B7 (D-2)
USBD_P: ESD1.2 (C1), R39.1, USBC.A6 (D+1), USBC.B6 (D+2)
USB_BOOT: R11.1, USB_BOOT.1
USB_SHIELD: C115.1, R68.1, USBC.S1 (SHIELD), USBC.S2 (SHIELD), USBC.S3 (SHIELD), USBC.S4 (SHIELD)
VBUS: C78.1, C79.1, ESD1.4 (C3), R12.1, R63.1, USBC.A4 (VBUS), USBC.A9 (VBUS1), USBC.B4 (VBUS3), USBC.B9 (VBUS2), VBUS.TP; also elsewhere on the board
VREF: C15.1, C16.1, IC3.3 (+IN), R17.1, REF1.1 (C), VREF1.TP

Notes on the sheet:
USB-C CONNECTOR
DECOUPLING
12MHZ CRYSTAL
RP2040 MCU
RP2040 FLASH
ADC VREF
DEBUG
Rev 1.0
David Sipos / DvidMakesThings

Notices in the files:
parts and their libraries:
Wurth_Connectors_WR-USB: Copyright: Würth Elektronik
COPYRIGHT: Copyright (C) 2025 Ultra Librarian. All rights reserved.
SparkFun-Retired: Licensing: Creative Commons ShareAlike 4.0 International - https://creativecommons.org/licenses/by-sa/4.0
